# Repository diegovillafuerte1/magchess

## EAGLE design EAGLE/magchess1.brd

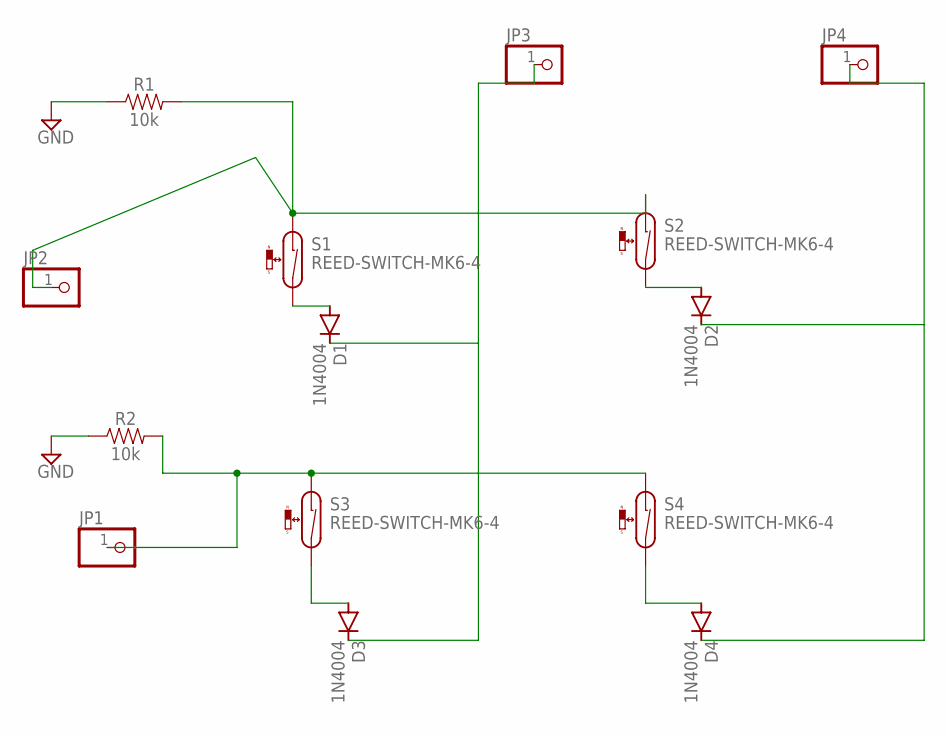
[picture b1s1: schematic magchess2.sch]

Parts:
D1, D2, D3, D4: 1N4004; DO41-10
JP1, JP2, JP3, JP4: PINHD-1X1; 1X01
R1, R2: 10k; AXIAL-0.3
S1, S2, S3, S4: REED-SWITCH-MK6-4; MK6-4

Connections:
GND: R1.P$1 (1), R2.P$1 (1)
unnamed: JP2.1, R1.P$2 (2), S1.1, S2.1
unnamed: JP1.1, R2.P$2 (2), S3.1, S4.1
unnamed: D1.A, S1.2
unnamed: D3.A, S3.2
unnamed: D4.A, S4.2
unnamed: D2.A, S2.2
unnamed: D2.C, D4.C, JP4.1
unnamed: D1.C, D3.C, JP3.1

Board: 2 copper layers, 14 parts (0 on the bottom side), 9 nets, no tracks yet.

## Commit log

2019-02-01 Add eagle files
2019-02-01 Add Arduino files
2019-02-02 Add full board arduino script
2019-02-02 add full board
2019-02-02 fix syntax, add send to pi empty method
2019-02-02 fix filestructure
2019-03-08 figured out how to work around relaly small garbage

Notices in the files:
parts and their libraries:
SparkFun-Resistors: Licensing: Creative Commons ShareAlike 4.0 International - https://creativecommons.org/licenses/by-sa/4.0
